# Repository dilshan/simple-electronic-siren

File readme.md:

# Simple Transistor-Based Electronic Siren

This project provides a discrete transistor implementation of a multi-tone electronic siren, offering an easy-to-build and low-cost solution that replicates alarm effects found in classic two-timer NE556 siren circuits. It serves as a practical alternative to rare *UM3561* and *UM3562* sound generator ICs.

The design uses only standard *BC548* / *BC558* transistors, resistors, and capacitors—making it easy to build with commonly available components.

A full assembly and test demonstration is available on [YouTube](https://youtu.be/mPkqBXPQGk4). Full details of this project are available at [blog post in here](https://jayakody2000lk.blogspot.com/2025/09/a-simple-transistor-based-electronic.html). 

---

## Features
- Three siren effects
- Adjustable sweep rate via potentiometer
- Operates from **6V** - **12V DC** supply
- Drives a small speaker (16Ω – 32Ω)
- All through-hole components for easy assembly

## PCB
This project PCB was sponsored by **PCBWay**. You can [order the PCB directly from PCBWay’s project sharing space](https://www.pcbway.com/project/shareproject/W282856ASV37_electronic_siren_09_07_2025_0b272f0c.html).

## License
This project is released under the [**Creative Commons Attribution 4.0 International**](https://github.com/dilshan/simple-electronic-siren#CC-BY-4.0-1-ov-file).

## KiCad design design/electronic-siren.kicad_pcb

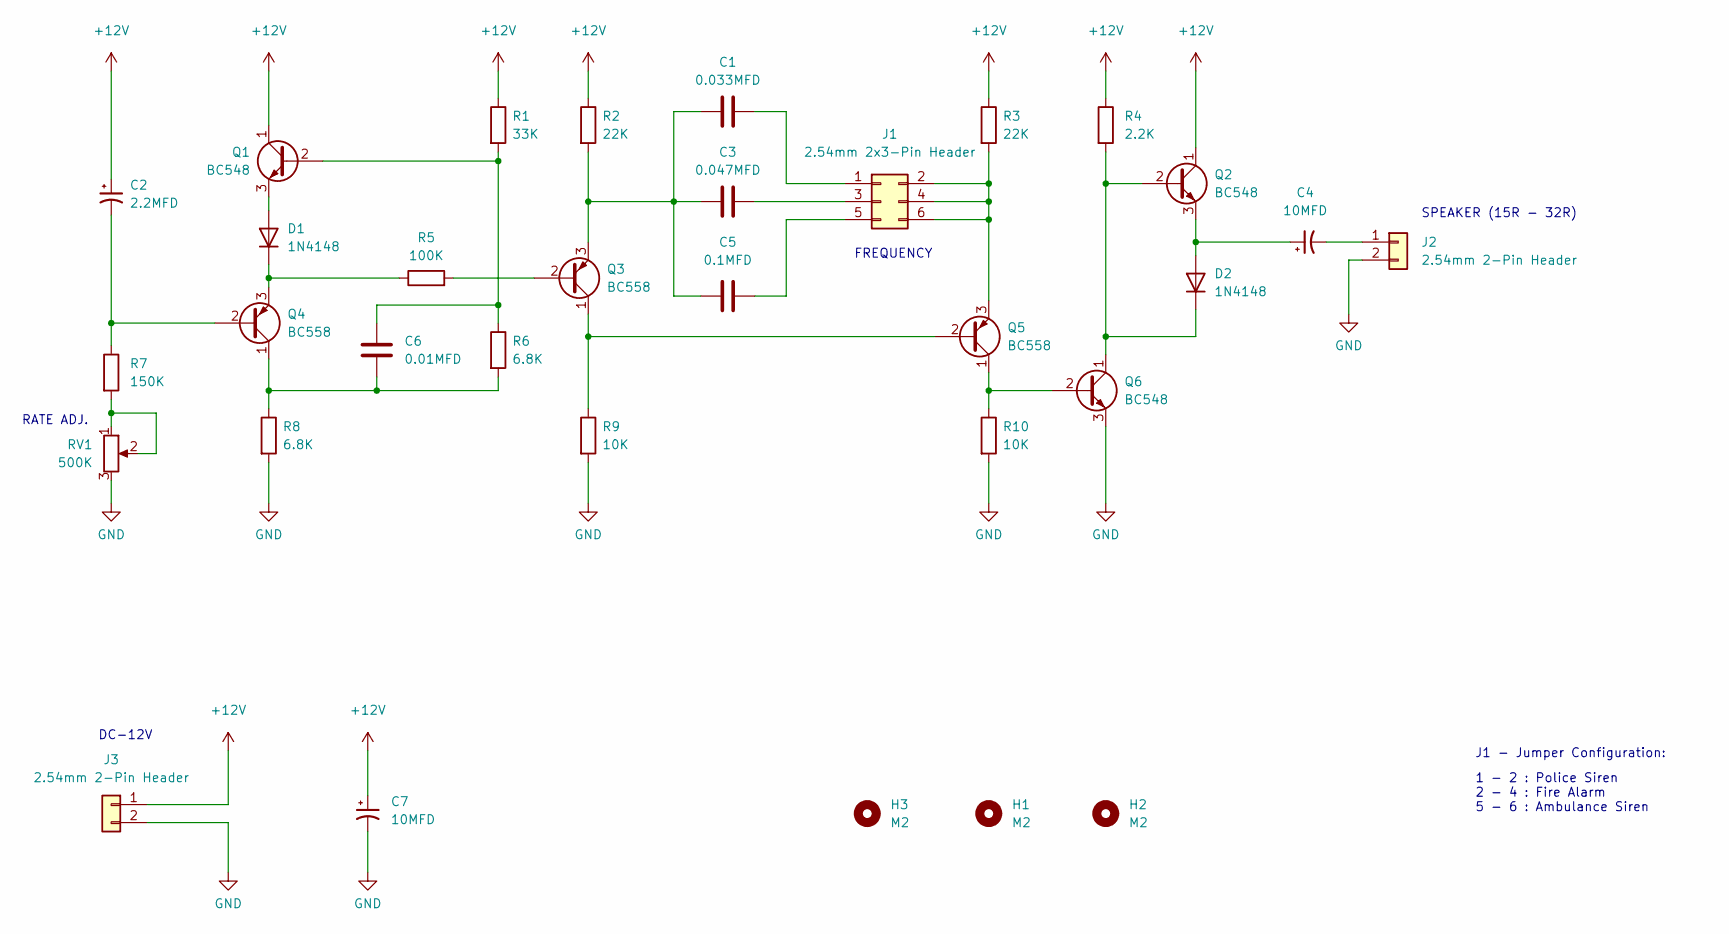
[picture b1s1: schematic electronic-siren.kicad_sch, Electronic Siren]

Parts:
C1: 0.033MFD; C_Rect_L7.0mm_W3.5mm_P5.00mm
C2: 2.2MFD; CP_Radial_D5.0mm_P2.00mm
C3: 0.047MFD; C_Rect_L9.0mm_W3.6mm_P7.50mm_MKT
C4, C7: 10MFD; CP_Radial_D5.0mm_P2.00mm
C5: 0.1MFD; C_Rect_L9.0mm_W4.2mm_P7.50mm_MKT
C6: 0.01MFD; C_Disc_D5.0mm_W2.5mm_P2.50mm
D1, D2: 1N4148; D_DO-35_SOD27_P7.62mm_Horizontal
H1, H2, H3: M2; MountingHole_2.2mm_M2
J1: 2.54mm 2x3-Pin Header; PinHeader_2x03_P2.54mm_Vertical
J2, J3: 2.54mm 2-Pin Header; PinHeader_1x02_P2.54mm_Vertical
Q1, Q2, Q6: BC548; TO-92_Inline
Q3, Q4, Q5: BC558; TO-92_Inline
R1: 33K; R_Axial_DIN0207_L6.3mm_D2.5mm_P10.16mm_Horizontal
R2, R3: 22K; R_Axial_DIN0207_L6.3mm_D2.5mm_P10.16mm_Horizontal
R4: 2.2K; R_Axial_DIN0207_L6.3mm_D2.5mm_P10.16mm_Horizontal
R5: 100K; R_Axial_DIN0207_L6.3mm_D2.5mm_P10.16mm_Horizontal
R6, R8: 6.8K; R_Axial_DIN0207_L6.3mm_D2.5mm_P10.16mm_Horizontal
R7: 150K; R_Axial_DIN0207_L6.3mm_D2.5mm_P10.16mm_Horizontal
R9, R10: 10K; R_Axial_DIN0207_L6.3mm_D2.5mm_P10.16mm_Horizontal
RV1: 500K; Potentiometer_Runtron_RM-065_Vertical

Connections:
+12V: C2.1, C7.1, J3.1, Q1.1 (C), Q2.1 (C), R1.1, R2.1, R3.1, R4.1
GND: C7.2, J2.2, J3.2, Q6.3 (E), R8.2, R9.2, R10.2, RV1.3
unnamed: D1.2 (A), Q1.3 (E)
unnamed: D1.1 (K), Q4.3 (E), R5.1
unnamed: C4.1, D2.2 (A), Q2.3 (E)
unnamed: D2.1 (K), Q2.2 (B), Q6.1 (C), R4.2
unnamed: C1.2, J1.1
unnamed: J1.2, J1.4, J1.6, Q5.3 (E), R3.2
unnamed: C3.2, J1.3
unnamed: C5.2, J1.5
unnamed: C4.2, J2.1
unnamed: C6.1, Q1.2 (B), R1.2, R6.1
unnamed: Q3.2 (B), R5.2
unnamed: Q3.1 (C), Q5.2 (B), R9.1
unnamed: C1.1, C3.1, C5.1, Q3.3 (E), R2.2
unnamed: C2.2, Q4.2 (B), R7.1
unnamed: C6.2, Q4.1 (C), R6.2, R8.1
unnamed: Q5.1 (C), Q6.2 (B), R10.1
unnamed: R7.2, RV1.1, RV1.2

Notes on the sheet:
DC-12V
RATE ADJ.
FREQUENCY
SPEAKER (15R - 32R)
1 - 2 : Police Siren 2 - 4 : Fire Alarm 5 - 6 : Ambulance Siren
J1 - Jumper Configuration:

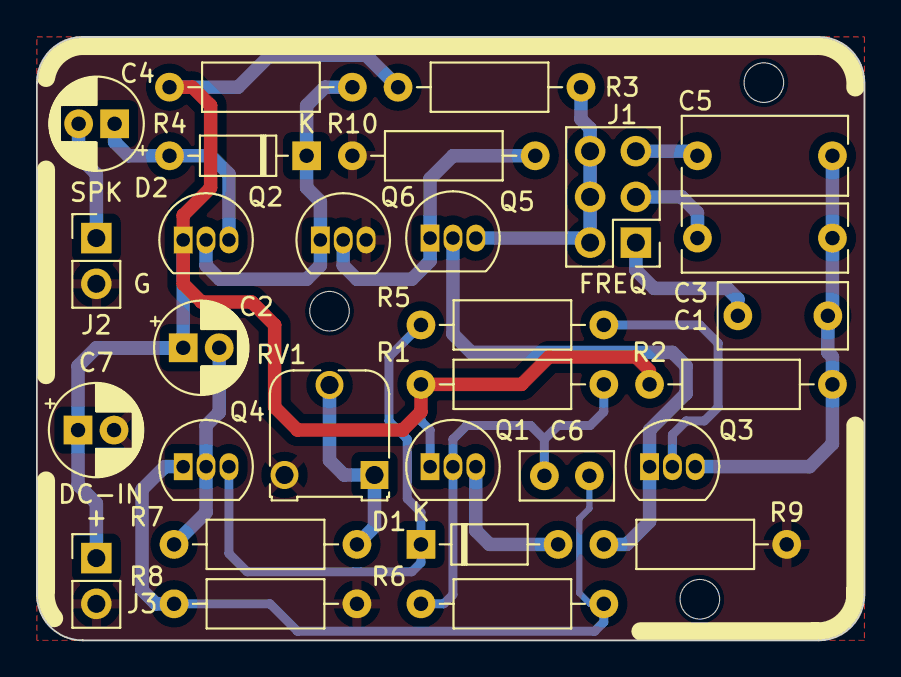
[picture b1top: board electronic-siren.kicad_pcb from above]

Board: 2 copper layers, 46.0 x 33.5 mm, 32 parts (0 on the bottom side), 19 nets.

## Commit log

2025-03-18 Add initial version of design files.
2025-09-13 Add schematic in PDF format.
2025-09-13 Add initial version of readme file.
2025-09-13 Add license file.
2025-09-13 Add license file link to readme file.
2025-09-13 Add image of the prototype build.
2025-09-13 Add BoM.
2025-09-13 Update BoM with standard component names.
2025-09-14 Add PCBWay order link to readme file.
2025-09-14 Add image to the readme file.
2025-09-14 Fix column name issue in BoM
2025-09-14 Update readme.md with blog link.
